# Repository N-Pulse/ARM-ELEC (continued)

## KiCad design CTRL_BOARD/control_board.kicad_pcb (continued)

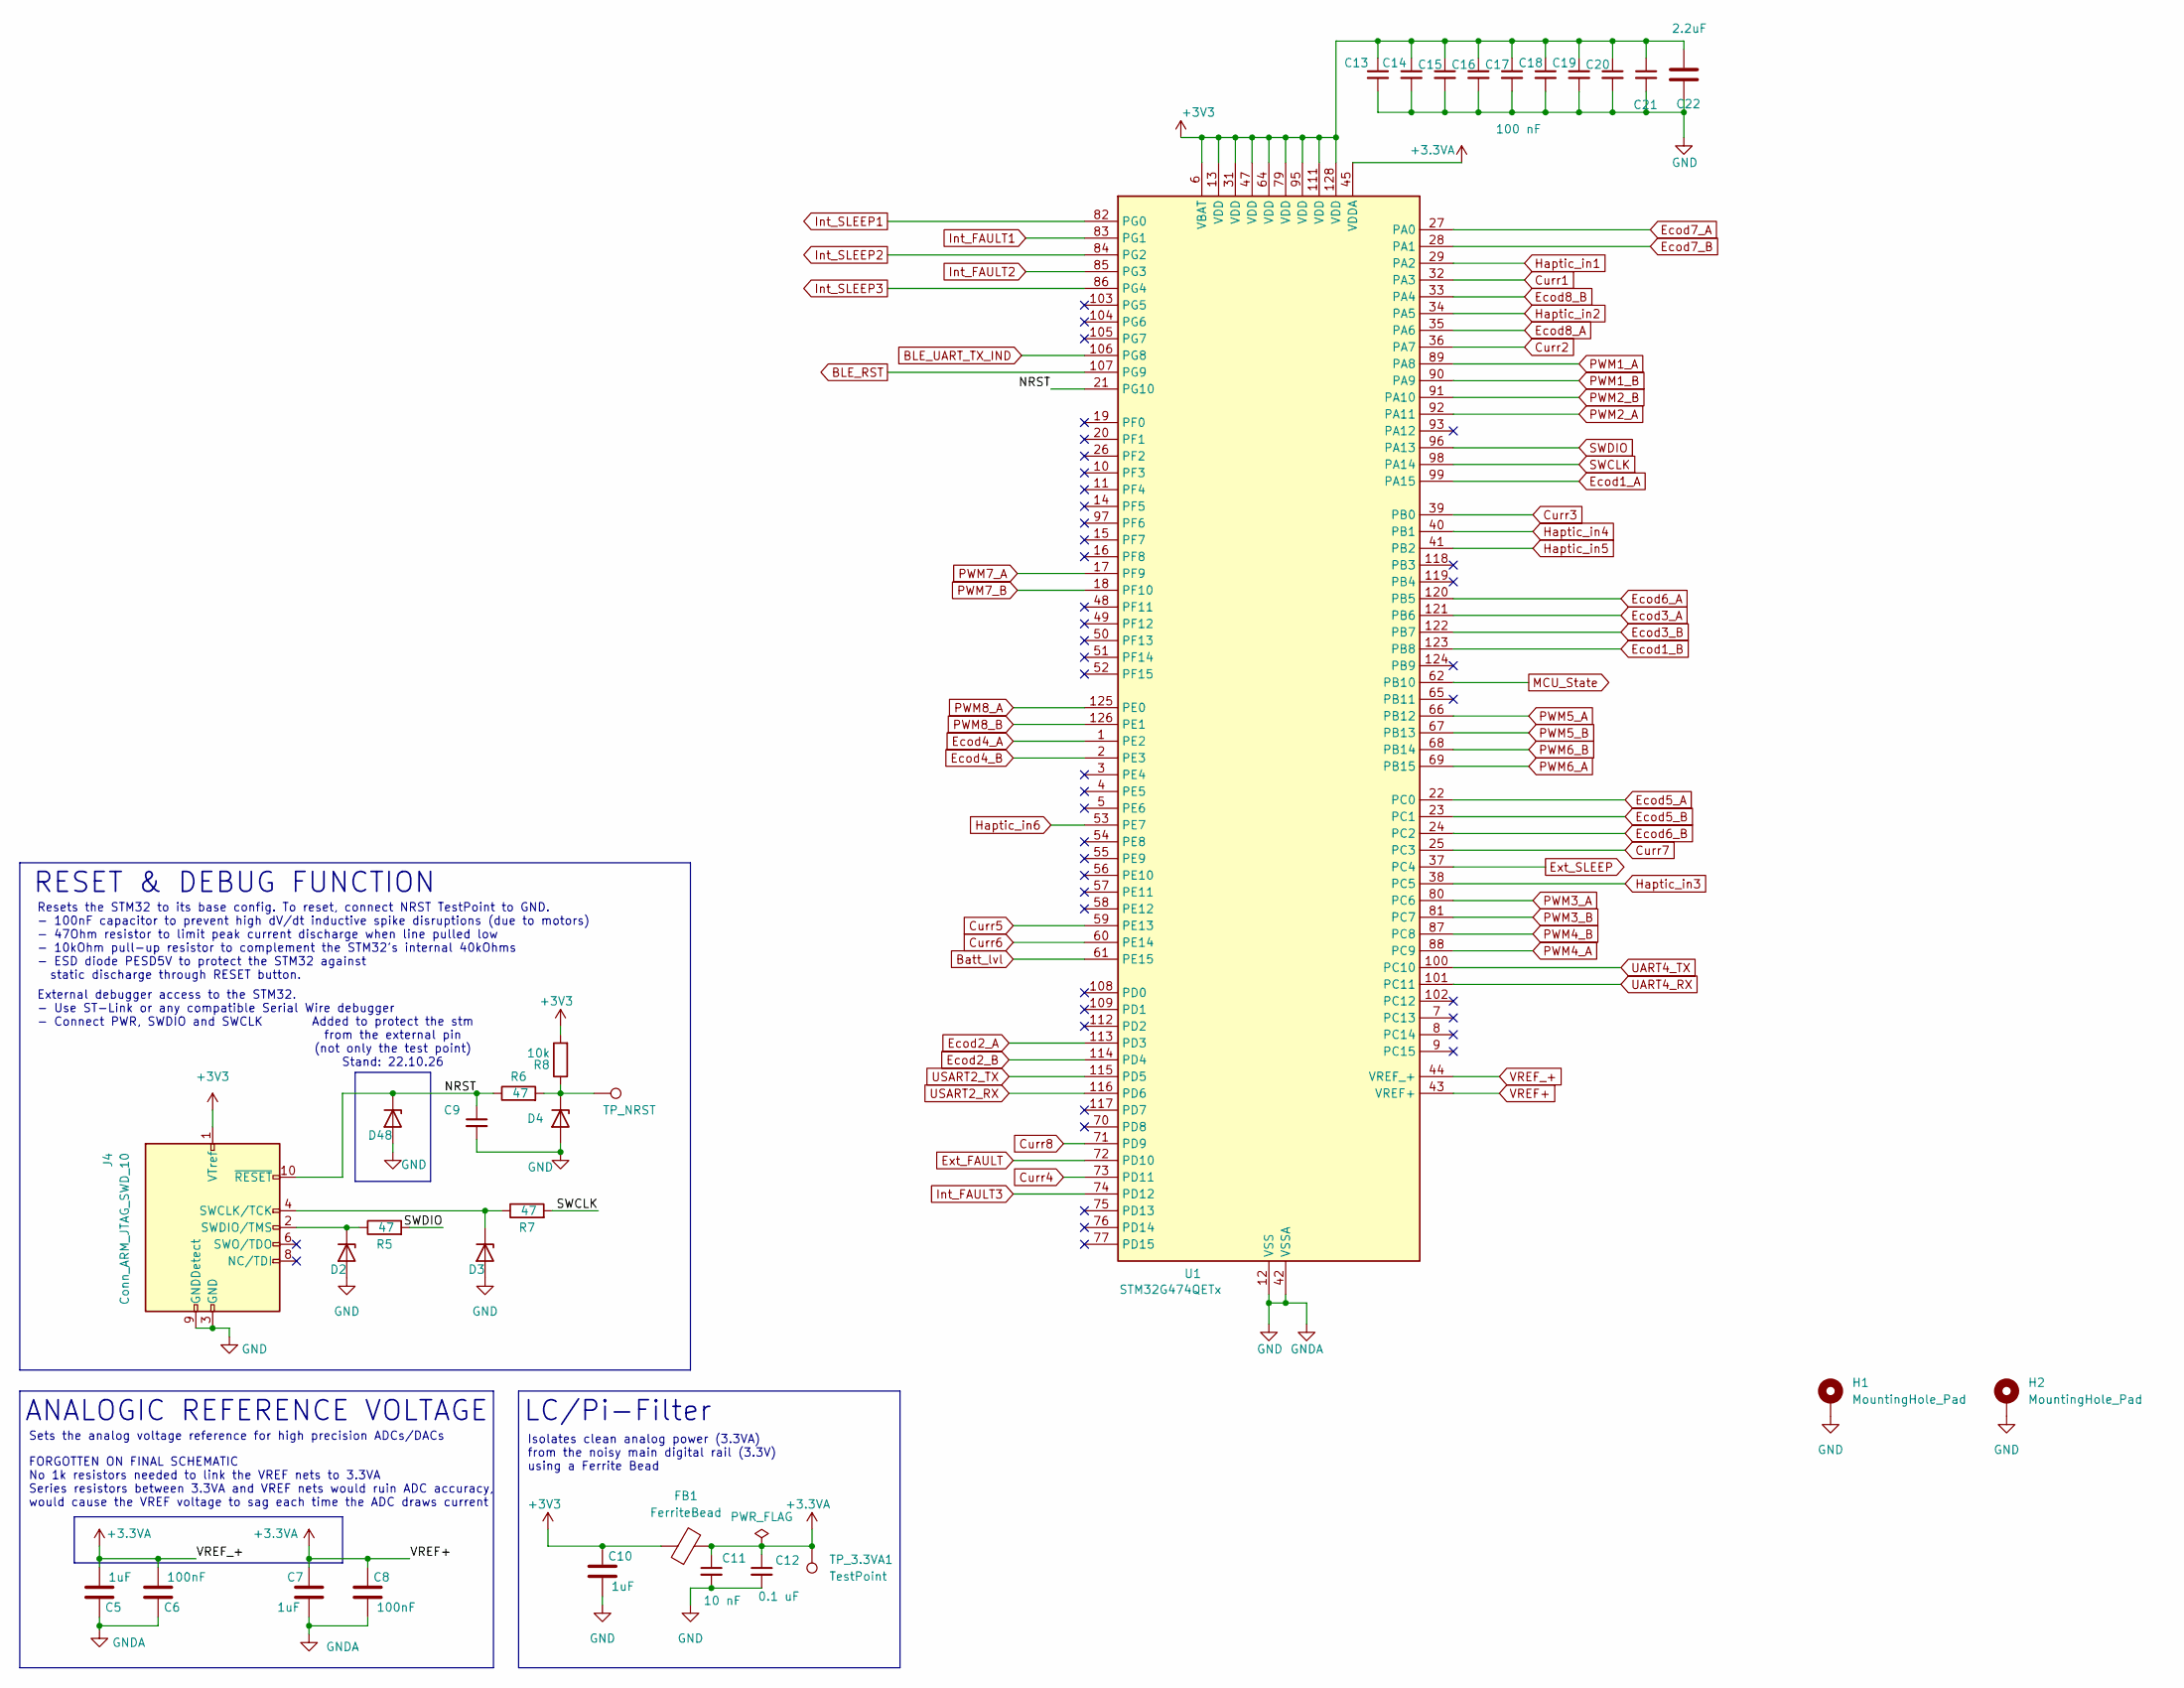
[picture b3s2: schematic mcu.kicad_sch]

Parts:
C5, C7, C10: 1uF; C_0402_1005Metric
C6, C8: 100nF; C_0402_1005Metric
C9, C13, C14, C15, C16, C17, C18, C19, C20, C21: 100 nF; C_0402_1005Metric
C11: 10 nF; C_0402_1005Metric
C12: 0.1 uF; C_0402_1005Metric
C22: 2.2uF; C_0603_1608Metric
D2, D3, D4, D48: PESD5V0L1UL; D_SOD-882
FB1: FerriteBead; L_0603_1608Metric
H1, H2: MountingHole_Pad; MountingHole_2.2mm_M2_Pad_Via
J4: Conn_ARM_JTAG_SWD_10; PinHeader_2x05_P1.27mm_Vertical_SMD
R5, R6, R7: 47; R_0402_1005Metric
R8: 10k; R_0402_1005Metric
TP_3.3VA1: TestPoint; TestPoint_THTPad_D1.5mm_Drill0.7mm
TP_NRST1: TP_NRST; TestPoint_THTPad_D1.5mm_Drill0.7mm
U1: STM32G474QETx; LQFP-128_14x14mm_P0.4mm

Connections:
+3V3: C10.1, C13.1, C14.1, C15.1, C16.1, C17.1, C18.1, C19.1, C20.1, C21.1, C22.1, FB1.1, J4.1 (VTref), R8.2, U1.6 (VBAT), U1.13 (VDD), U1.31 (VDD), U1.47 (VDD), U1.64 (VDD), U1.79 (VDD), U1.95 (VDD), U1.111 (VDD), U1.128 (VDD); also elsewhere on the board
/MCU/NRST: C9.1, D48.1 (K), J4.10 (~RESET), R6.1, U1.21 (PG10)
BLE_RST: U1.107 (PG9); also elsewhere on the board
BLE_UART_TX_IND: U1.106 (PG8); also elsewhere on the board
Batt_lvl: U1.61 (PE15); also elsewhere on the board
Curr1: U1.32 (PA3); also elsewhere on the board
Curr2: U1.36 (PA7); also elsewhere on the board
Curr3: U1.39 (PB0); also elsewhere on the board
Curr4: U1.73 (PD11); also elsewhere on the board
Curr5: U1.59 (PE13); also elsewhere on the board
Curr6: U1.60 (PE14); also elsewhere on the board
Curr7: U1.25 (PC3); also elsewhere on the board
Curr8: U1.71 (PD9); also elsewhere on the board
Ecod1_A: U1.99 (PA15); also elsewhere on the board
Ecod1_B: U1.123 (PB8); also elsewhere on the board
Ecod2_A: U1.113 (PD3); also elsewhere on the board
Ecod2_B: U1.114 (PD4); also elsewhere on the board
Ecod3_A: U1.121 (PB6); also elsewhere on the board
Ecod3_B: U1.122 (PB7); also elsewhere on the board
Ecod4_A: U1.1 (PE2); also elsewhere on the board
Ecod4_B: U1.2 (PE3); also elsewhere on the board
Ecod5_A: U1.22 (PC0); also elsewhere on the board
Ecod5_B: U1.23 (PC1); also elsewhere on the board
Ecod6_A: U1.120 (PB5); also elsewhere on the board
Ecod6_B: U1.24 (PC2); also elsewhere on the board
Ecod7_A: U1.27 (PA0); also elsewhere on the board
Ecod7_B: U1.28 (PA1); also elsewhere on the board
Ecod8_A: U1.35 (PA6); also elsewhere on the board
Ecod8_B: U1.33 (PA4); also elsewhere on the board
Ext_FAULT: U1.72 (PD10); also elsewhere on the board
Ext_SLEEP: U1.37 (PC4); also elsewhere on the board
GND: C5.1, C6.1, C7.2, C8.2, C9.2, C10.2, C11.2, C12.2, C13.2, C14.2, C15.2, C16.2, C17.2, C18.2, C19.2, C20.2, C21.2, C22.2, D2.2 (A), D3.2 (A), D4.2 (A), D48.2 (A), H1.1 (1_1), H2.1 (1_1), J4.3 (GND), J4.5 (GND), J4.9 (GNDDetect), U1.12 (VSS), U1.30 (VSS), U1.42 (VSSA), U1.46 (VSS), U1.63 (VSS), U1.78 (VSS), U1.94 (VSS), U1.110 (VSS), U1.127 (VSS); also elsewhere on the board
Haptic_in1: U1.29 (PA2); also elsewhere on the board
Haptic_in2: U1.34 (PA5); also elsewhere on the board
Haptic_in3: U1.38 (PC5); also elsewhere on the board
Haptic_in4: U1.40 (PB1); also elsewhere on the board
Haptic_in5: U1.41 (PB2); also elsewhere on the board
Haptic_in6: U1.53 (PE7); also elsewhere on the board
Int_FAULT1: U1.83 (PG1); also elsewhere on the board
Int_FAULT2: U1.85 (PG3); also elsewhere on the board
Int_FAULT3: U1.74 (PD12); also elsewhere on the board
Int_SLEEP1: U1.82 (PG0); also elsewhere on the board
Int_SLEEP2: U1.84 (PG2); also elsewhere on the board
Int_SLEEP3: U1.86 (PG4); also elsewhere on the board
MCU_State: U1.62 (PB10); also elsewhere on the board
unnamed: D2.1 (K), J4.2 (SWDIO/TMS), R5.1
unnamed: D3.1 (K), J4.4 (SWCLK/TCK), R7.1
unnamed: D4.1 (K), R6.2, R8.1, TP_NRST1.1 (1_1)
PWM1_A: U1.89 (PA8); also elsewhere on the board
PWM1_B: U1.90 (PA9); also elsewhere on the board
PWM2_A: U1.92 (PA11); also elsewhere on the board
PWM2_B: U1.91 (PA10); also elsewhere on the board
PWM3_A: U1.80 (PC6); also elsewhere on the board
PWM3_B: U1.81 (PC7); also elsewhere on the board
PWM4_A: U1.88 (PC9); also elsewhere on the board
PWM4_B: U1.87 (PC8); also elsewhere on the board
PWM5_A: U1.66 (PB12); also elsewhere on the board
PWM5_B: U1.67 (PB13); also elsewhere on the board
PWM6_A: U1.69 (PB15); also elsewhere on the board
PWM6_B: U1.68 (PB14); also elsewhere on the board
PWM7_A: U1.17 (PF9); also elsewhere on the board
PWM7_B: U1.18 (PF10); also elsewhere on the board
PWM8_A: U1.125 (PE0); also elsewhere on the board
PWM8_B: U1.126 (PE1); also elsewhere on the board
SWCLK: R7.2, U1.98 (PA14)
SWDIO: R5.2, U1.96 (PA13)
UART4_RX: U1.101 (PC11); also elsewhere on the board
UART4_TX: U1.100 (PC10); also elsewhere on the board
USART2_RX: U1.116 (PD6); also elsewhere on the board
USART2_TX: U1.115 (PD5); also elsewhere on the board
VREF+: C5.2, C6.2, C7.1, C8.1, C11.1, C12.1, FB1.2, TP_3.3VA1.1 (1_1), U1.43 (VREF+), U1.44 (VREF_+), U1.45 (VDDA)

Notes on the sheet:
Isolates clean analog power (3.3VA) from the noisy main digital rail (3.3V) using a Ferrite Bead
Added to protect the stm from the external pin (not only the test point) Stand: 22.10.26
External debugger access to the STM32. - Use ST-Link or any compatible Serial Wire debugger - Connect PWR, SWDIO and SWCLK
Sets the analog voltage reference for high precision ADCs/DACs
Resets the STM32 to its base config. To reset, connect NRST TestPoint to GND. - 100nF capacitor to prevent high dV/dt inductive spike disruptions (due to motors) - 47Ohm resistor to limit peak current discharge when line pulled low - 10kOhm pull-up resistor to complement the STM32's internal 40kOhm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
LC/Pi-Filter
ANALOGIC REFERENCE VOLTAGE
RESET & DEBUG FUNCTION
FORGOTTEN ON FINAL SCHEMATIC No 1k resistors needed to link the VREF nets to 3.3VA Series resistors between 3.3VA and VREF nets would ruin ADC accuracy, would cause the VREF voltage to sag each time the ADC draws current

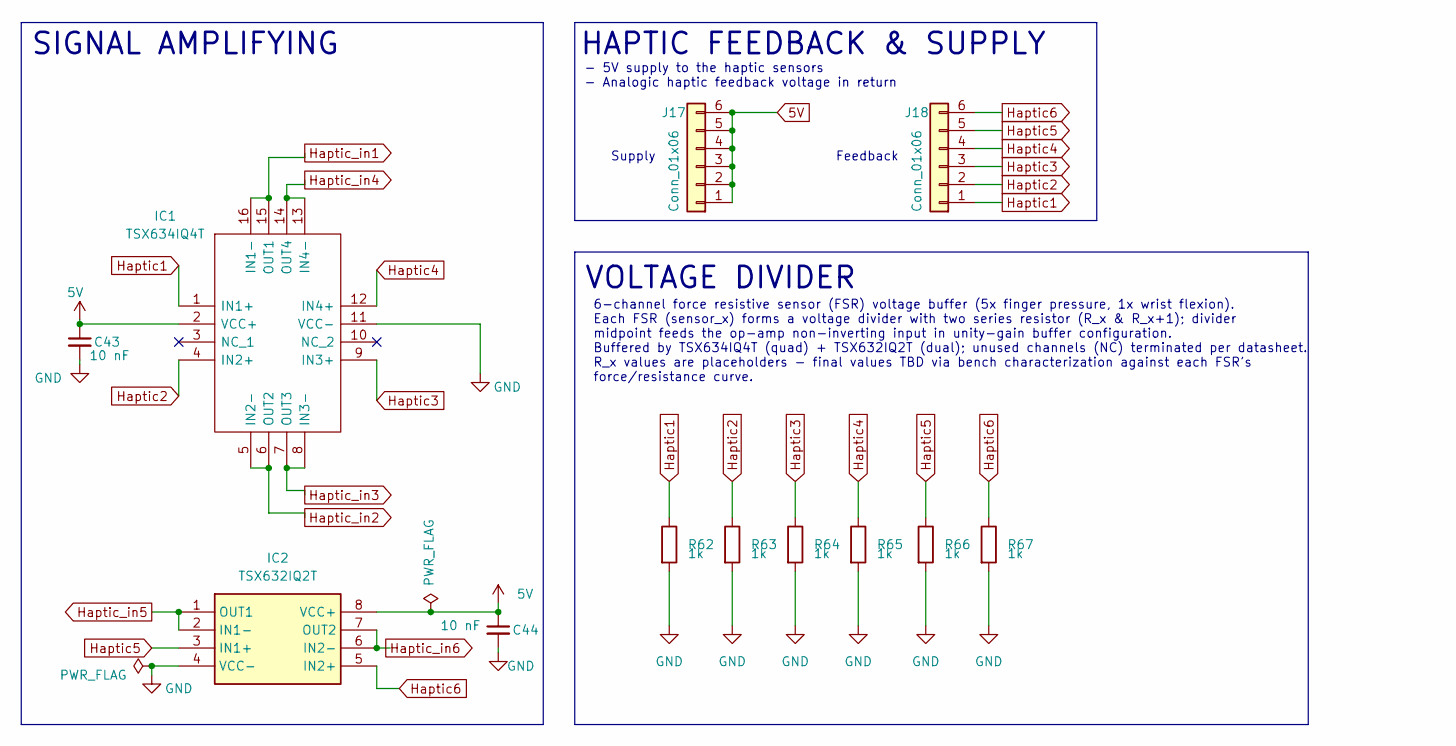
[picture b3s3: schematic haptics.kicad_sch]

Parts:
C43, C44: 10 nF; C_0402_1005Metric
IC1: TSX634IQ4T; QFN50P300X300X65-16N-D; Mouser Part Number 511-TSX634IQ4T
IC2: TSX632IQ2T; SON50P200X200X80-8N; Manufacturer_Part_Number TSX632IQ2T; Mouser Part Number 511-TSX632IQ2T
J17, J18: Conn_01x06; CONN_5037630000-SD_06_MOL
R62, R63, R64, R65, R66, R67: 1k; R_0402_1005Metric

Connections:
5V: C43.1, C44.1, IC1.2 (VCC+), IC2.8 (VCC+), J17.1, J17.2, J17.3, J17.4, J17.5, J17.6; also elsewhere on the board
GND: C43.2, C44.2, IC1.11 (VCC-), IC2.4 (VCC-), R62.2, R63.2, R64.2, R65.2, R66.2, R67.2; also elsewhere on the board
Haptic1: IC1.1 (IN1+), J18.1, R62.1
Haptic2: IC1.4 (IN2+), J18.2, R63.1
Haptic3: IC1.9 (IN3+), J18.3, R64.1
Haptic4: IC1.12 (IN4+), J18.4, R65.1
Haptic5: IC2.3 (IN1+), J18.5, R66.1
Haptic6: IC2.5 (IN2+), J18.6, R67.1
Haptic_in1: IC1.15 (OUT1), IC1.16 (IN1-); also elsewhere on the board
Haptic_in2: IC1.5 (IN2-), IC1.6 (OUT2); also elsewhere on the board
Haptic_in3: IC1.7 (OUT3), IC1.8 (IN3-); also elsewhere on the board
Haptic_in4: IC1.13 (IN4-), IC1.14 (OUT4); also elsewhere on the board
Haptic_in5: IC2.1 (OUT1), IC2.2 (IN1-); also elsewhere on the board
Haptic_in6: IC2.6 (IN2-), IC2.7 (OUT2); also elsewhere on the board

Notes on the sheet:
Supply
SIGNAL AMPLIFYING
HAPTIC FEEDBACK & SUPPLY
6-channel force resistive sensor (FSR) voltage buffer (5x finger pressure, 1x wrist flexion). Each FSR (sensor_x) forms a voltage divider with two series resistor (R_x & R_x+1); divider midpoint feeds the op-amp non-inverting input in unity-gain buffer configuration. Buffered by TSX634IQ4T (quad) +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
- 5V supply to the haptic sensors - Analogic haptic feedback voltage in return
VOLTAGE DIVIDER
Feedback

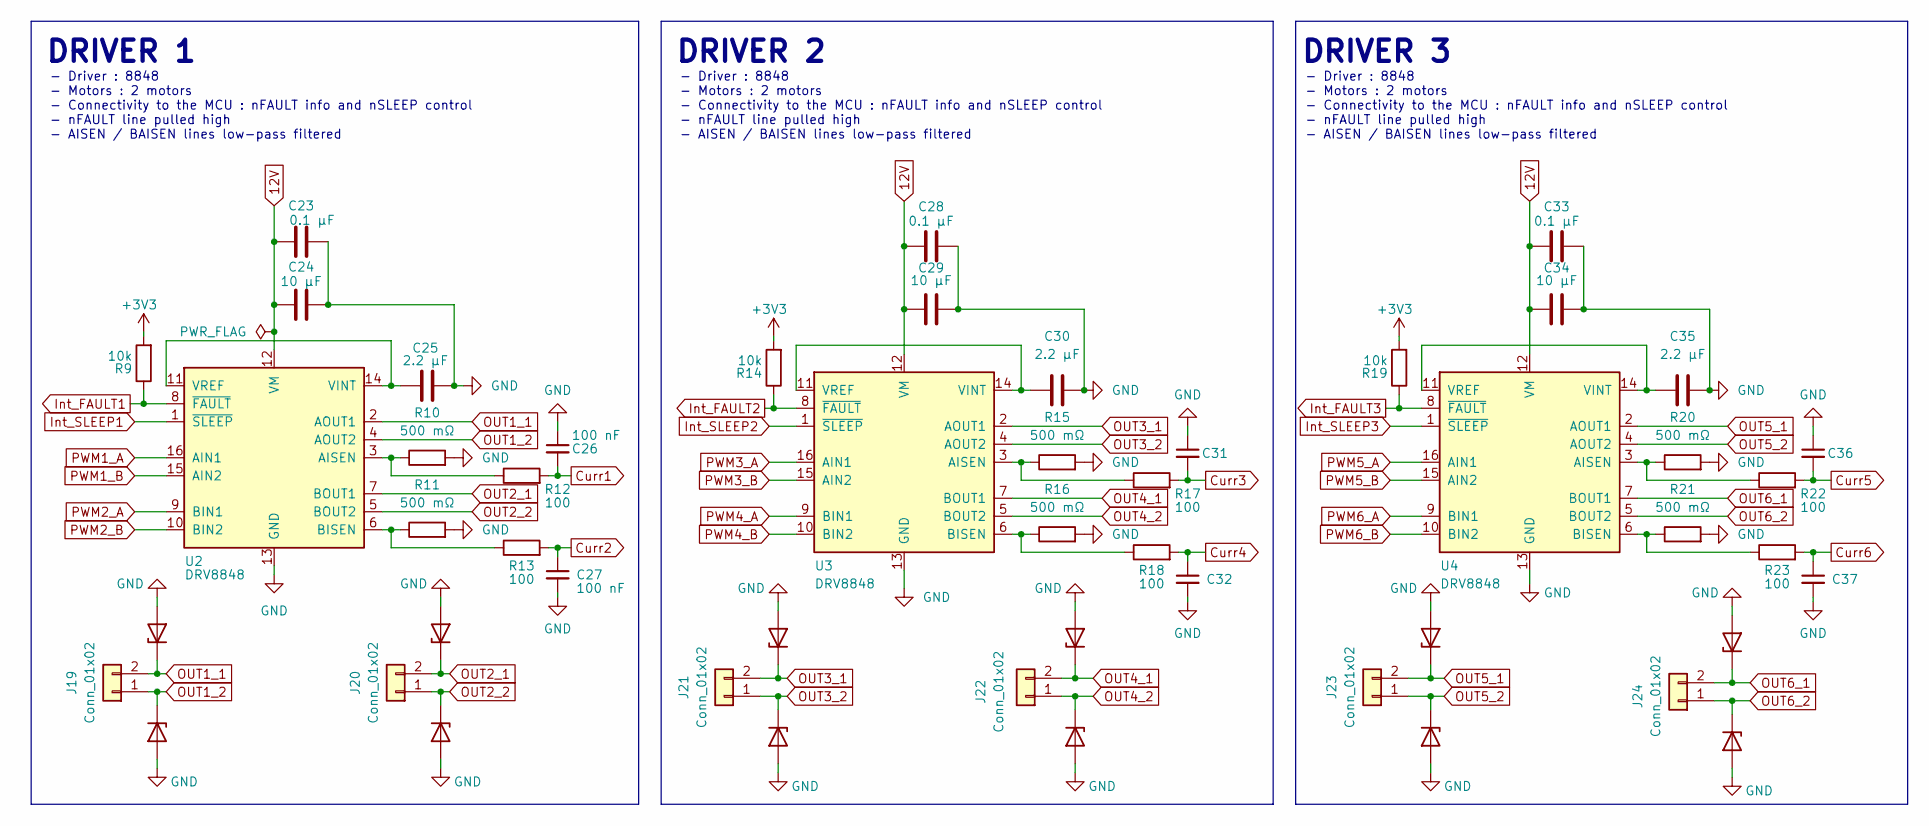
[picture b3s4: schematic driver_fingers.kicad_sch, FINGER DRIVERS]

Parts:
C23, C28, C33: 0.1 µF; C_0603_1608Metric
C24, C29, C34: 10 µF; C_0603_1608Metric
C25, C30, C35: 2.2 µF; C_0603_1608Metric
C26, C27, C31, C32, C36, C37: 100 nF; C_0402_1005Metric
D5, D6, D7, D8, D9, D10, D11, D12, D13, D14, D15, D16: PESD5V0L1UL; D_SOD-882
J19, J20, J21, J22, J23, J24: Conn_01x02; CONN_5037630000-SD_02_MOL
R9, R14, R19: 10k; R_0402_1005Metric
R10, R11, R15, R16, R20, R21: 500 mΩ; R_0402_1005Metric
R12, R13, R17, R18, R22, R23: 100; R_0402_1005Metric
U2, U3, U4: DRV8848; TSSOP-16-1EP_4.4x5mm_P0.65mm

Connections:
12V: C23.1, C24.1, C28.1, C29.1, C33.1, C34.1, U2.12 (VM), U3.12 (VM), U4.12 (VM); also elsewhere on the board
+3V3: R9.2, R14.2, R19.2; also elsewhere on the board
Curr1: C26.2, R12.2; also elsewhere on the board
Curr2: C27.1, R13.2; also elsewhere on the board
Curr3: C31.2, R17.2; also elsewhere on the board
Curr4: C32.1, R18.2; also elsewhere on the board
Curr5: C36.2, R22.2; also elsewhere on the board
Curr6: C37.1, R23.2; also elsewhere on the board
GND: C23.2, C24.2, C25.2, C26.1, C27.2, C28.2, C29.2, C30.2, C31.1, C32.2, C33.2, C34.2, C35.2, C36.1, C37.2, D5.2 (A), D6.2 (A), D7.2 (A), D8.2 (A), D9.2 (A), D10.2 (A), D11.2 (A), D12.2 (A), D13.2 (A), D14.2 (A), D15.2 (A), D16.2 (A), R10.2, R11.2, R15.2, R16.2, R20.2, R21.2, U2.13 (GND), U2.17 (GND), U3.13 (GND), U3.17 (GND), U4.13 (GND), U4.17 (GND); also elsewhere on the board
Int_FAULT1: R9.1, U2.8 (~FAULT); also elsewhere on the board
Int_FAULT2: R14.1, U3.8 (~FAULT); also elsewhere on the board
Int_FAULT3: R19.1, U4.8 (~FAULT); also elsewhere on the board
Int_SLEEP1: U2.1 (~SLEEP); also elsewhere on the board
Int_SLEEP2: U3.1 (~SLEEP); also elsewhere on the board
Int_SLEEP3: U4.1 (~SLEEP); also elsewhere on the board
unnamed: R10.1, R12.1, U2.3 (AISEN)
unnamed: R11.1, R13.1, U2.6 (BISEN)
unnamed: C25.1, U2.11 (VREF), U2.14 (VINT)
unnamed: R15.1, R17.1, U3.3 (AISEN)
unnamed: R16.1, R18.1, U3.6 (BISEN)
unnamed: C30.1, U3.11 (VREF), U3.14 (VINT)
unnamed: R20.1, R22.1, U4.3 (AISEN)
unnamed: R21.1, R23.1, U4.6 (BISEN)
unnamed: C35.1, U4.11 (VREF), U4.14 (VINT)
OUT1_1: D5.1 (K), J19.2, U2.2 (AOUT1)
OUT1_2: D6.1 (K), J19.1, U2.4 (AOUT2)
OUT2_1: D7.1 (K), J20.2, U2.7 (BOUT1)
OUT2_2: D8.1 (K), J20.1, U2.5 (BOUT2)
OUT3_1: D9.1 (K), J21.2, U3.2 (AOUT1)
OUT3_2: D10.1 (K), J21.1, U3.4 (AOUT2)
OUT4_1: D11.1 (K), J22.2, U3.7 (BOUT1)
OUT4_2: D12.1 (K), J22.1, U3.5 (BOUT2)
OUT5_1: D13.1 (K), J23.2, U4.2 (AOUT1)
OUT5_2: D14.1 (K), J23.1, U4.4 (AOUT2)
OUT6_1: D15.1 (K), J24.2, U4.7 (BOUT1)
OUT6_2: D16.1 (K), J24.1, U4.5 (BOUT2)
PWM1_A: U2.16 (AIN1); also elsewhere on the board
PWM1_B: U2.15 (AIN2); also elsewhere on the board
PWM2_A: U2.9 (BIN1); also elsewhere on the board
PWM2_B: U2.10 (BIN2); also elsewhere on the board
PWM3_A: U3.16 (AIN1); also elsewhere on the board
PWM3_B: U3.15 (AIN2); also elsewhere on the board
PWM4_A: U3.9 (BIN1); also elsewhere on the board
PWM4_B: U3.10 (BIN2); also elsewhere on the board
PWM5_A: U4.16 (AIN1); also elsewhere on the board
PWM5_B: U4.15 (AIN2); also elsewhere on the board
PWM6_A: U4.9 (BIN1); also elsewhere on the board
PWM6_B: U4.10 (BIN2); also elsewhere on the board

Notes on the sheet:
- Driver : 8848 - Motors : 2 motors - Connectivity to the MCU : nFAULT info and nSLEEP control - nFAULT line pulled high - AISEN / BAISEN lines low-pass filtered
DRIVER 2
DRIVER 3
DRIVER 1

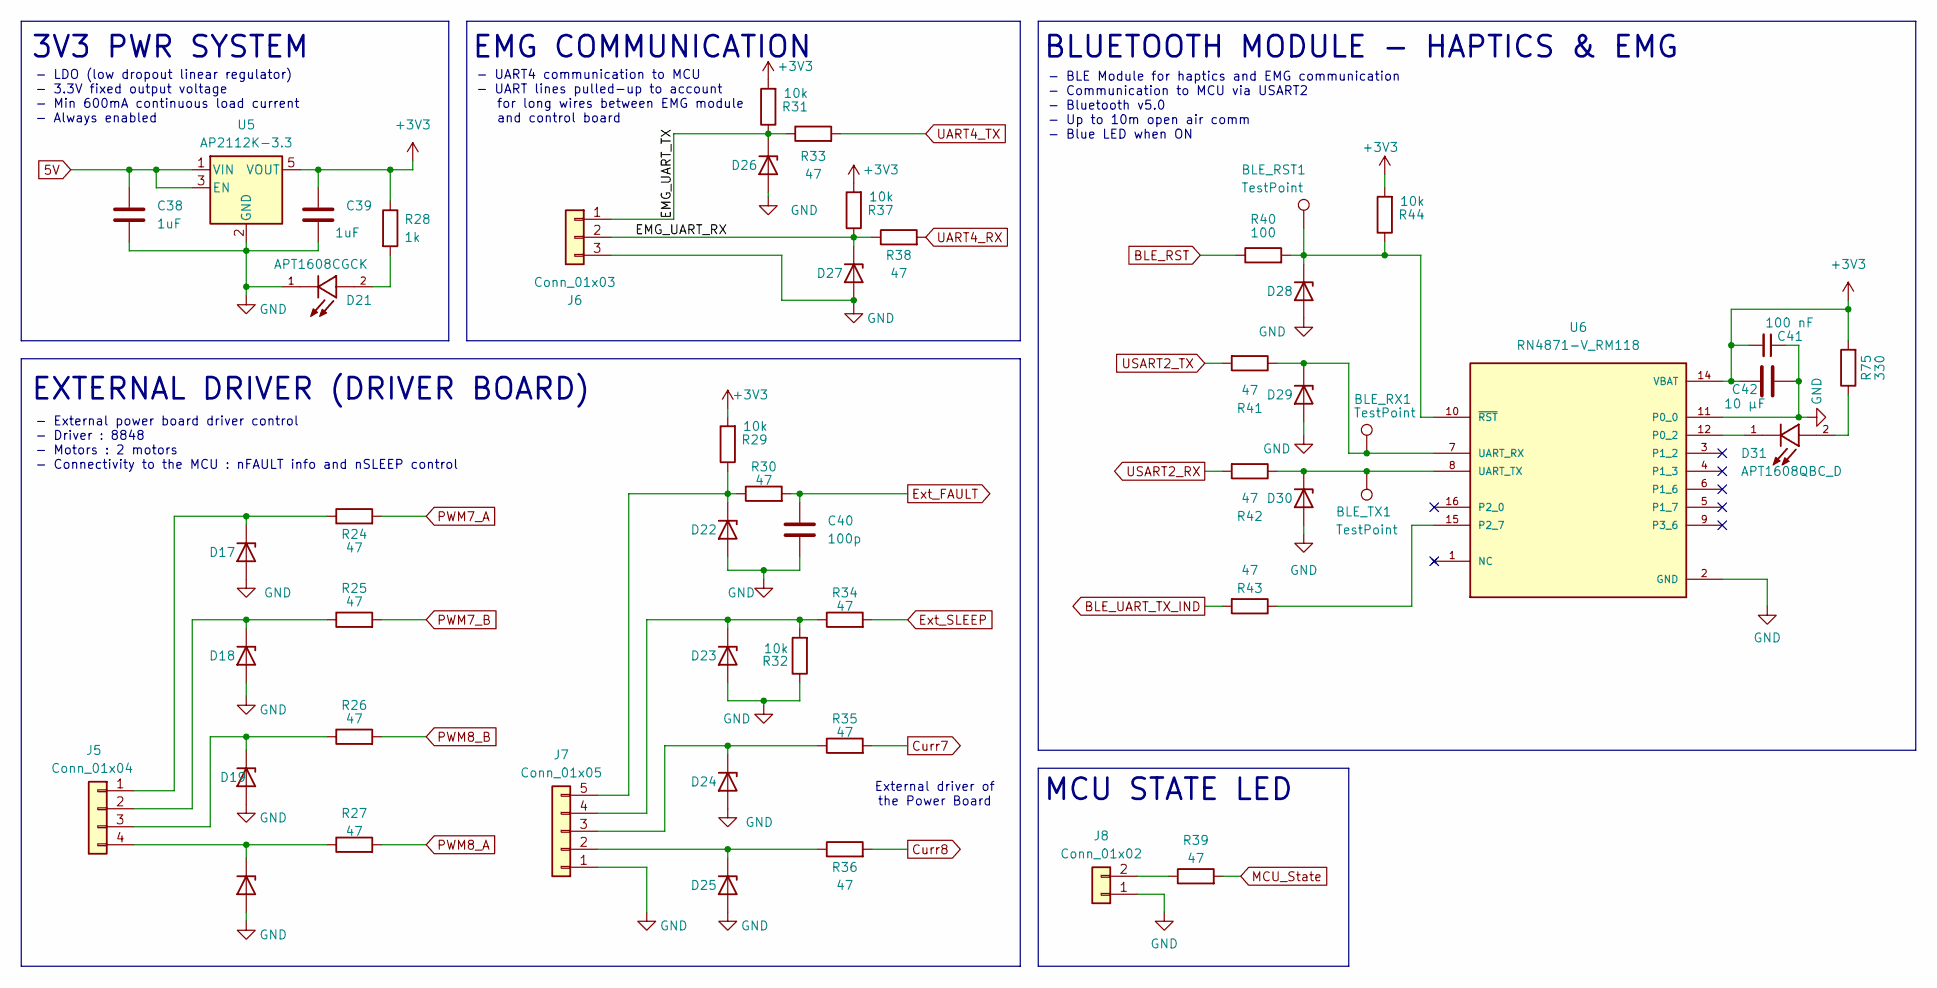
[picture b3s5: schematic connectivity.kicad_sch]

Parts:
BLE_RST1: TestPoint; TestPoint_THTPad_D1.5mm_Drill0.7mm
BLE_RX1: TestPoint; TestPoint_THTPad_D1.5mm_Drill0.7mm
BLE_TX1: TestPoint; TestPoint_THTPad_D1.5mm_Drill0.7mm
C38, C39: 1uF; C_0402_1005Metric
C40: 100p; C_0402_1005Metric
C41: 100 nF; C_0402_1005Metric
C42: 10 µF; C_0603_1608Metric
D17, D18, D19, D20, D22, D23, D24, D25, D26, D27, D28, D29, D30: PESD5V0L1UL; D_SOD-882
D21: APT1608CGCK; LED_APT1608CGCK; PARTREV V.20B
D31: APT1608QBC_D; LED_APT1608QBC_D; PARTREV V.20B
J5: Conn_01x04; CONN_5037630000-SD_04_MOL
J6: Conn_01x03; CONN_5037630000-SD_03_MOL
J7: Conn_01x05; CONN_5037630000-SD_05_MOL
J8: Conn_01x02; CONN_5037630000-SD_02_MOL
R24, R25, R26, R27, R30, R33, R34, R35, R36, R38, R39, R41, R42, R43: 47; R_0402_1005Metric
R28: 1k; R_0402_1005Metric
R29, R31, R32, R37, R44: 10k; R_0402_1005Metric
R40: 100; R_0402_1005Metric
R75: 330; R_0402_1005Metric
U5: AP2112K-3.3; SOT-23-5
U6: RN4871-V_RM118; XCVR_RN4871-V_RM118; PARTREV E

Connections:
5V: C38.1, U5.1 (VIN), U5.3 (EN); also elsewhere on the board
+3V3: C39.1, C41.2, C42.2, R28.1, R29.2, R31.2, R37.2, R44.2, R75.2, U5.5 (VOUT), U6.14 (VBAT); also elsewhere on the board
/CONNECTIVITY/EMG_UART_RX: D27.1 (K), J6.2, R37.1, R38.1
/CONNECTIVITY/EMG_UART_TX: D26.1 (K), J6.1, R31.1, R33.1
BLE_RST: R40.1; also elsewhere on the board
BLE_UART_TX_IND: R43.2; also elsewhere on the board
Curr7: R35.2; also elsewhere on the board
Curr8: R36.2; also elsewhere on the board
Ext_FAULT: C40.1, R30.2; also elsewhere on the board
Ext_SLEEP: R34.2; also elsewhere on the board
GND: C38.2, C39.2, C40.2, C41.1, C42.1, D17.2 (A), D18.2 (A), D19.2 (A), D20.2 (A), D21.1, D22.2 (A), D23.2 (A), D24.2 (A), D25.2 (A), D26.2 (A), D27.2 (A), D28.2 (A), D29.2 (A), D30.2 (A), J6.3, J7.1, J8.1, R32.1, U5.2 (GND), U6.2 (GND), U6.11 (P0_0), U6.13 (GND); also elsewhere on the board
MCU_State: R39.2; also elsewhere on the board
unnamed: D17.1 (K), J5.1, R24.1
unnamed: D18.1 (K), J5.2, R25.1
unnamed: D19.1 (K), J5.3, R26.1
unnamed: D20.1 (K), J5.4, R27.1
unnamed: D21.2, R28.2
unnamed: D22.1 (K), J7.5, R29.1, R30.1
unnamed: D23.1 (K), J7.4, R32.2, R34.1
unnamed: D24.1 (K), J7.3, R35.1
unnamed: D25.1 (K), J7.2, R36.1
unnamed: BLE_RST1.1 (1_1), D28.1 (K), R40.2, R44.1, U6.10 (~RST)
unnamed: BLE_RX1.1 (1_1), D29.1 (K), R41.1, U6.7 (UART_RX)
unnamed: BLE_TX1.1 (1_1), D30.1 (K), R42.1, U6.8 (UART_TX)
unnamed: D31.2, R75.1
unnamed: J8.2, R39.1
unnamed: D31.1, U6.12 (P0_2)
unnamed: R43.1, U6.15 (P2_7)
PWM7_A: R24.2; also elsewhere on the board
PWM7_B: R25.2; also elsewhere on the board
PWM8_A: R27.2; also elsewhere on the board
PWM8_B: R26.2; also elsewhere on the board
UART4_RX: R38.2; also elsewhere on the board
UART4_TX: R33.2; also elsewhere on the board
USART2_RX: R42.2; also elsewhere on the board
USART2_TX: R41.2; also elsewhere on the board

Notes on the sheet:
External driver of the Power Board
MCU STATE LED
3V3 PWR SYSTEM
EMG COMMUNICATION
- LDO (low dropout linear regulator) - 3.3V fixed output voltage - Min 600mA continuous load current - Always enabled
BLUETOOTH MODULE - HAPTICS & EMG
EXTERNAL DRIVER (DRIVER BOARD)
- BLE Module for haptics and EMG communication - Communication to MCU via USART2 - Bluetooth v5.0 - Up to 10m open air comm - Blue LED when ON
- UART4 communication to MCU - UART lines pulled-up to account for long wires between EMG module and control board
- External power board driver control - Driver : 8848 - Motors : 2 motors - Connectivity to the MCU : nFAULT info and nSLEEP control

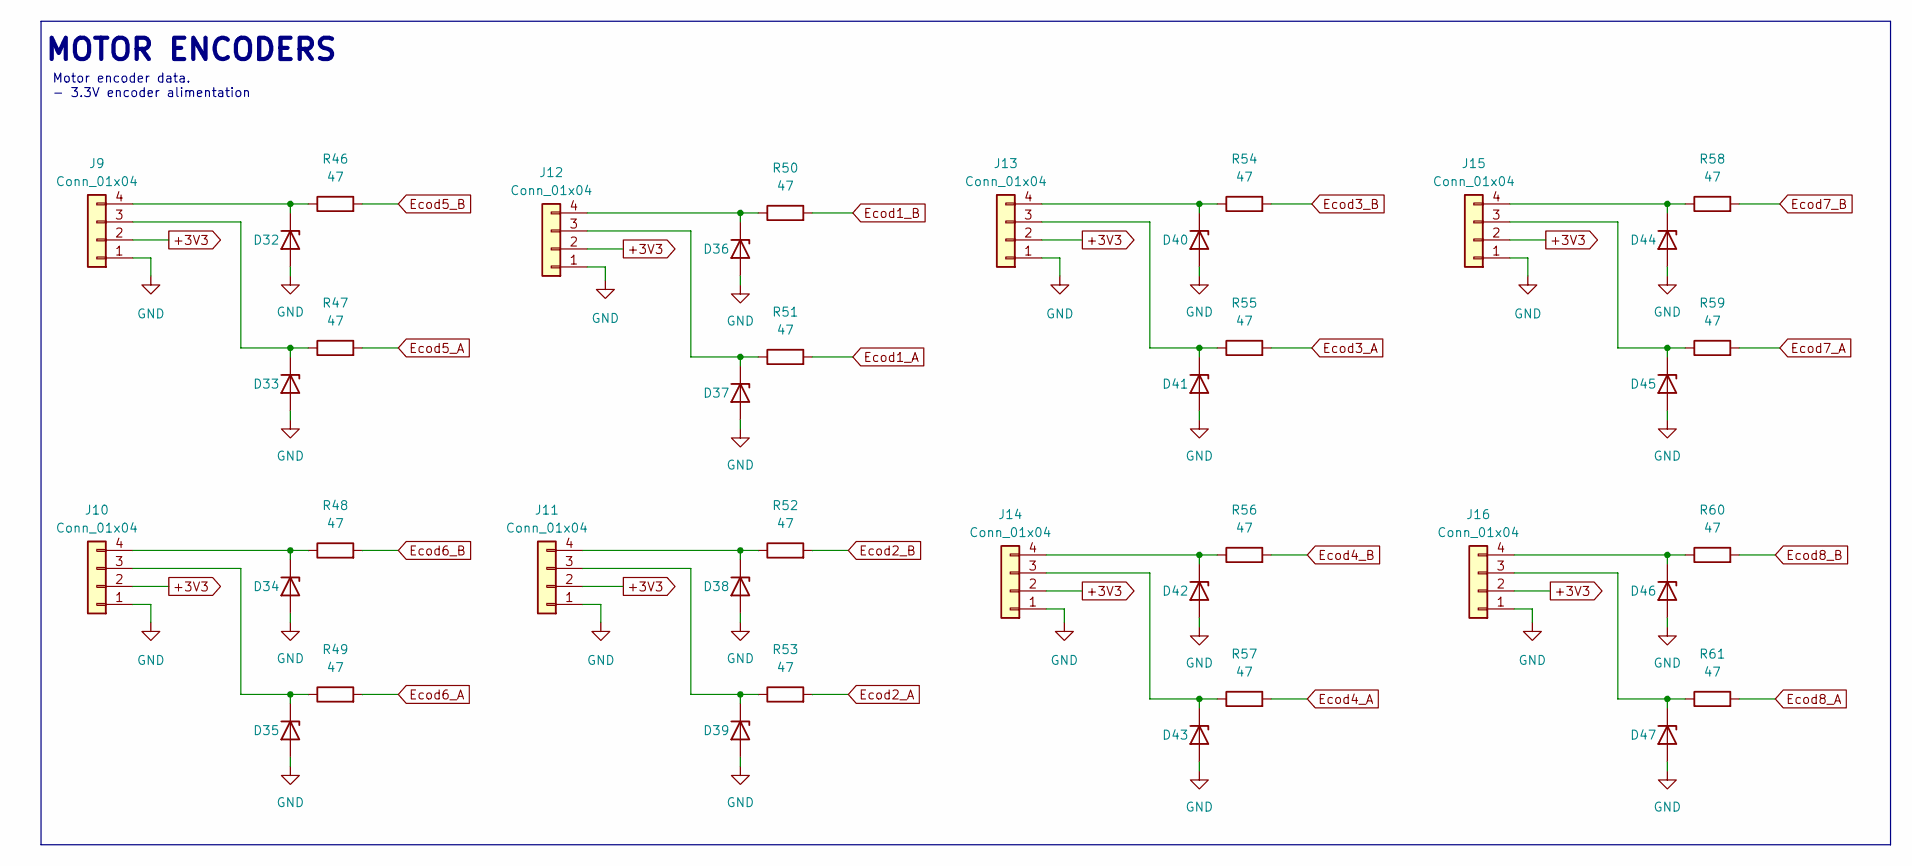
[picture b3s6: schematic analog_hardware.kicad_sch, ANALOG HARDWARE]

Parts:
D32, D33, D34, D35, D36, D37, D38, D39, D40, D41, D42, D43, D44, D45, D46, D47: PESD5V0L1UL; D_SOD-882
J9, J10, J11, J12, J13, J14, J15, J16: Conn_01x04; CONN_5037630000-SD_04_MOL
R46, R47, R48, R49, R50, R51, R52, R53, R54, R55, R56, R57, R58, R59, R60, R61: 47; R_0402_1005Metric

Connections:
+3V3: J9.2, J10.2, J11.2, J12.2, J13.2, J14.2, J15.2, J16.2; also elsewhere on the board
Ecod1_A: R51.2; also elsewhere on the board
Ecod1_B: R50.2; also elsewhere on the board
Ecod2_A: R53.2; also elsewhere on the board
Ecod2_B: R52.2; also elsewhere on the board
Ecod3_A: R55.2; also elsewhere on the board
Ecod3_B: R54.2; also elsewhere on the board
Ecod4_A: R57.2; also elsewhere on the board
Ecod4_B: R56.2; also elsewhere on the board
Ecod5_A: R47.2; also elsewhere on the board
Ecod5_B: R46.2; also elsewhere on the board
Ecod6_A: R49.2; also elsewhere on the board
Ecod6_B: R48.2; also elsewhere on the board
Ecod7_A: R59.2; also elsewhere on the board
Ecod7_B: R58.2; also elsewhere on the board
Ecod8_A: R61.2; also elsewhere on the board
Ecod8_B: R60.2; also elsewhere on the board
GND: D32.2 (A), D33.2 (A), D34.2 (A), D35.2 (A), D36.2 (A), D37.2 (A), D38.2 (A), D39.2 (A), D40.2 (A), D41.2 (A), D42.2 (A), D43.2 (A), D44.2 (A), D45.2 (A), D46.2 (A), D47.2 (A), J9.1, J10.1, J11.1, J12.1, J13.1, J14.1, J15.1, J16.1; also elsewhere on the board
unnamed: D32.1 (K), J9.4, R46.1
unnamed: D33.1 (K), J9.3, R47.1
unnamed: D34.1 (K), J10.4, R48.1
unnamed: D35.1 (K), J10.3, R49.1
unnamed: D36.1 (K), J12.4, R50.1
unnamed: D37.1 (K), J12.3, R51.1
unnamed: D38.1 (K), J11.4, R52.1
unnamed: D39.1 (K), J11.3, R53.1
unnamed: D40.1 (K), J13.4, R54.1
unnamed: D41.1 (K), J13.3, R55.1
unnamed: D42.1 (K), J14.4, R56.1
unnamed: D43.1 (K), J14.3, R57.1
unnamed: D44.1 (K), J15.4, R58.1
unnamed: D45.1 (K), J15.3, R59.1
unnamed: D46.1 (K), J16.4, R60.1
unnamed: D47.1 (K), J16.3, R61.1

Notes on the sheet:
MOTOR ENCODERS
Motor encoder data. - 3.3V encoder alimentation

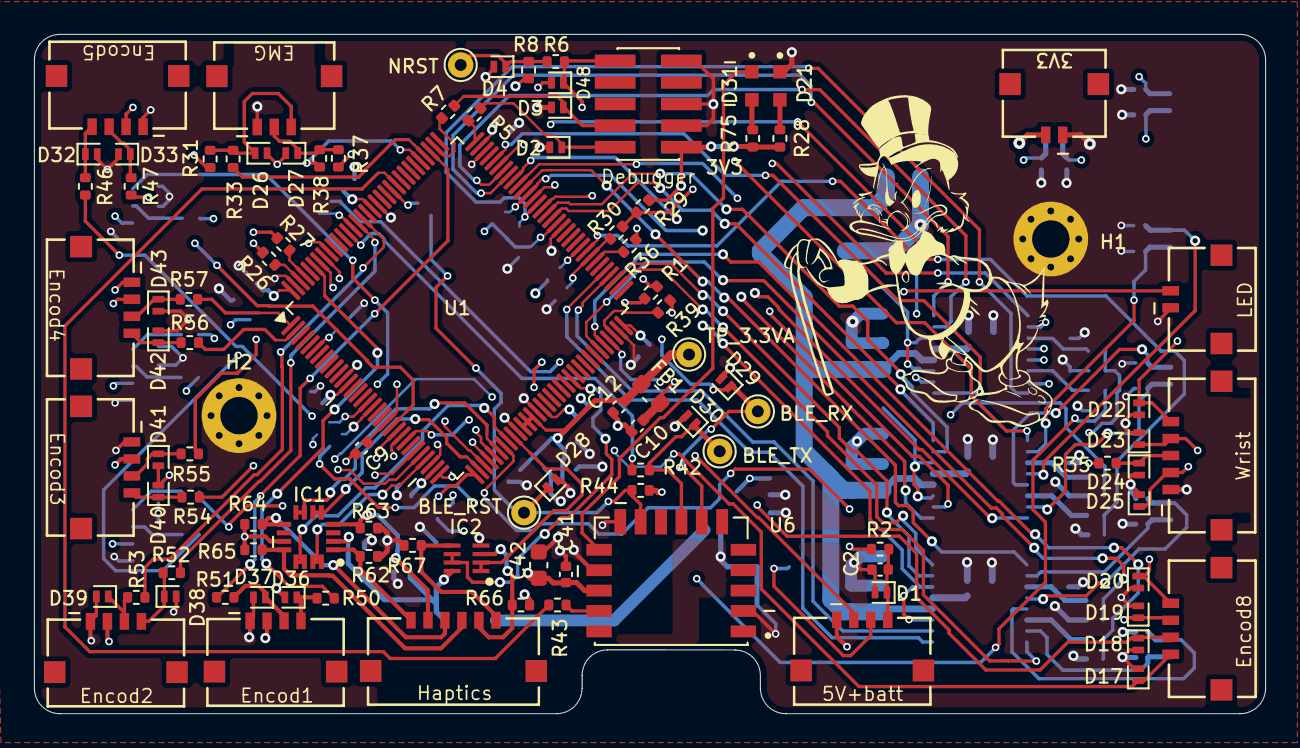
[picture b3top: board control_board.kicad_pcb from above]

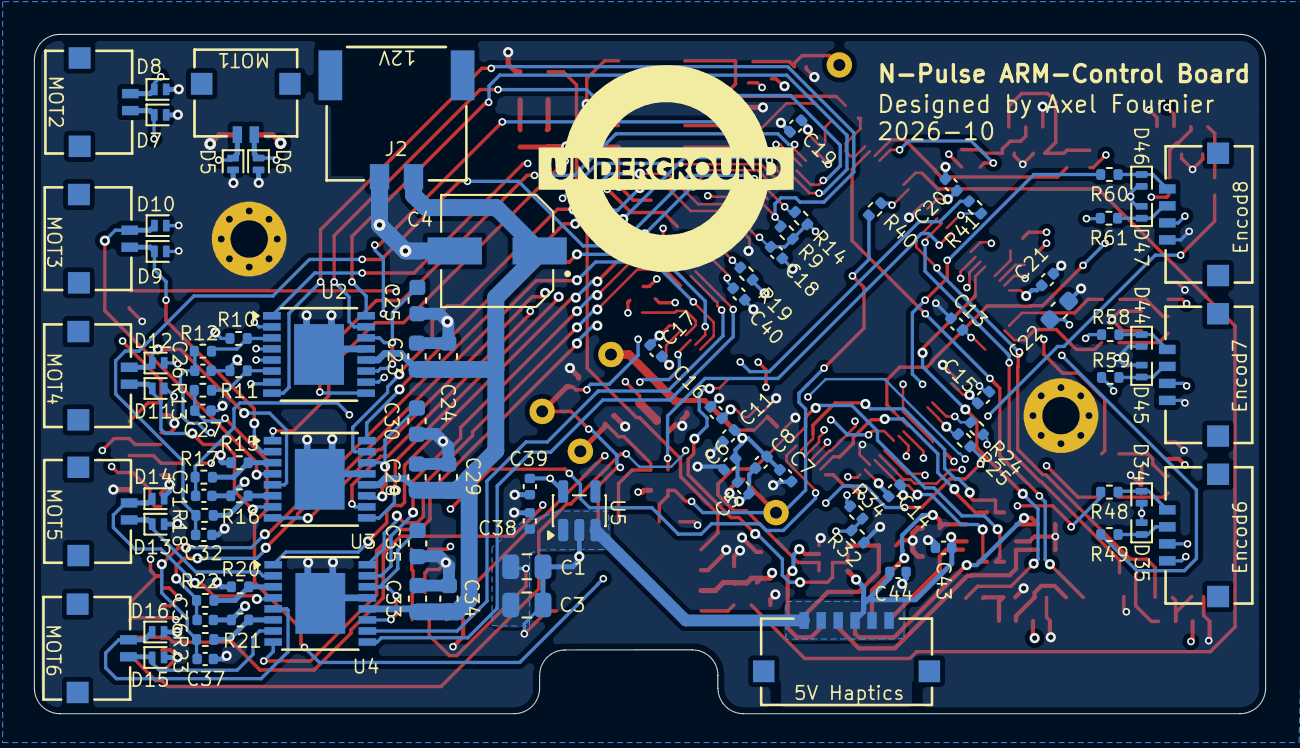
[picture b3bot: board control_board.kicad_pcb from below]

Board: 6 copper layers, 72.5 x 40.0 mm, 197 parts (98 on the bottom side), 136 nets.
